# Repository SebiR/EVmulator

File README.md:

> [!CAUTION]
> This project includes dangerous voltages of 230V/400V, a bit of tinkering and (public) charging infrastructure.
> Build and use this project only if you know what you are doing. I am not liable for injuries or damages!

# EVmulator
A small PCB to go into IEC 62196 Typ 2 EV charging plugs to emulate a car to use a charging station as a normal outlet.

It's currently running with an ATTiny85, although an ATTiny25 will suffice. In the future it might be done with an ATTiny10.

## Features
* Two LEDs as status indicator
* Automatic switch from connected to charging
* 13 or 32A selectable current
* EVSE Pilot monitoring
* Completely powered by the pilot signal

## Function

The EVmulator simulates a connected car for the EVSE (electric vehicle supply equipment, the wallbox)

The EVSE outputs a 1kHz square wave signal with ±12V referenced to PE with 1000 ohms impedance on the CP (Control Pilot) pin and measures the voltage of the CP line.
As the EVmulator has a 1300 ohms resitor to PE, the positive voltage of the CP line is pulled to 9V and the EVSE detects a connected car.

After connecting, the EVmulator will detect the 1kHz PWM signal on the CP line and after approx. 5 seconds of PWM, the second restitor with 4.7kohms will be connected in parallel to the first resitor. As the voltage on the CP line drops to 6V, the EVSE will recognize the emulator as a charging car.

More information on Type 2 Signaling can be found here (in German):
https://www.goingelectric.de/wiki/Typ2-Signalisierung-und-Steckercodierung/

To end the charging process, a magnet is placed on the plug, opening a reed switch and signaling the end of charge to the charger.

## Usage

### Connection
Connect the three terminals of the EVmulator with the according pins of your IEC 62196 Type 2 male plug:

| Pin  | Function           | Description                                  |
|------|--------------------|----------------------------------------------|
| PP  | Control Pilot         | maximum current of the cable defined by a resistor |
| PE  | Earth | Commond ground for communication      |
| CP  | Control Pilot     | Communication line between car and charger |

### Solder Jumpers

There are two SMT solder jumpers located on the component side of the PCB:<br>
**SJ1** bypasses the internal reed switch in case you want to use a key switch or a push button to stop the charging process. Use NC (normally closed "openener" switches).<br>
**SJ2 LED** has to be closed after flashing the microcontroller to activate the status LED. The TPI programming interface is a bit finicky when it comes to other components on the programming lines.<br>

And there's one solder jumper on the side with the reed switch:<br>
**SJ3 13/32A** let's you select between a max. current of 13A or 32A depending on your application. Always make sure to use rated cables and connectors!

### Inside the plug

Drill a 3mm hole in the plug and put the LED through it. Fix the board with a bit of silicone or hot glue and you're done!

If you want, you can add a label:

### In the field
Just connect you Type 2 plug to the wallbox or charging station and authorize the charging process as you would normally.
The EVmulator will signal the charger that a car has been connected and that it is charging.<br>

To stop the charging process, place a magnet over the reed switch and unplug the plug.

| LED Behavior        | State      |
|---------------------|---------------|
| Quick blink (1 ms flash every ~32 ms) | Idling, waiting for CP signal          |
| Slow blink (1 ms flash every ~125 ms) | Checking if the CP signal is valid       |
| Very slow blink (1 ms flash every ~1 s) | Charging        |

## Firmware

The firmware is written for the ATTiny10 microcontroller using the Arduino IDE and the <a href="https://github.com/technoblogy/attiny10core">attiny10core</a> board definitions.

### Hardware Configuration

| Pin  | Function           | Description                                  |
|------|--------------------|----------------------------------------------|
| PB0  | LED Output         | Blinks to indicate system state              |
| PB1  | CHARGE_ON (Output) | Controls a MOSFET for to signal Charging state      |
| PB2  | Frequency Input     | Connected to external ~1kHz square wave, also Timer0 clock source |

### System Clock and Power Settings

- The system clock is derived from the 128 kHz Watchdog oscillator.
- A clock prescaler divides this to 32 kHz system frequency.
- The ADC and analog comparator are disabled to save power.
- The microcontroller primarily stays in `SLEEP_MODE_IDLE`, waking periodically via the Watchdog Timer interrupt.

### State Machine

The firmware operates in three states:

1. **IDLE**  
   - Wakes every ~32 ms via WDT.
   - If no external clock signal is detected (TCNT0 == 0), stays in IDLE.
   - If a clock signal is consistently present for 10 cycles, transitions to MEASURE.

2. **MEASURE**  
   - Wakes every ~125 ms.
   - Measures frequency using Timer0 (externally clocked).
   - If the frequency is above 500 Hz for 10 cycles, transitions to CHARGE.
   - Remains in MEASURE as long as signal is present and below 500 Hz.

3. **CHARGE**  
   - Wakes approximately every second.
   - Enables the CHARGE_ON MOSFET (PB1 high).
   - If frequency drops below 500 Hz for 5 consecutive cycles, reverts to MEASURE.

### LED Signal Behavior

The LED (on PB0) provides visual feedback for debugging and operational awareness:

| LED Behavior        | State(s)      | Meaning                                   |
|---------------------|---------------|-------------------------------------------|
| Quick blink (1 ms flash every ~32 ms) | IDLE          | Signal inactive or low frequency detected |
| Slow blink (1 ms flash every ~125 ms) | MEASURE       | Signal detected, measuring frequency       |
| Very slow blink (1 ms flash every ~1 s) | CHARGE        | Charging enabled, monitoring signal        |

All blinking is implemented by flashing the LED for 1 ms during each WDT interrupt.

### Power Optimization

- All unnecessary peripherals (ADC, comparator) are disabled.
- WDT interval is adjusted dynamically based on state.
- Sleep modes and minimal active time are used to reduce power consumption.
- Timer0 uses an asynchronous external clock, allowing operation even in low-power modes.

## Other

During development, I also created the <a href="https://github.com/SebiR/EVSE_Emulator_Shield">EVSE Emulator Shield</a> to test the EVmulator

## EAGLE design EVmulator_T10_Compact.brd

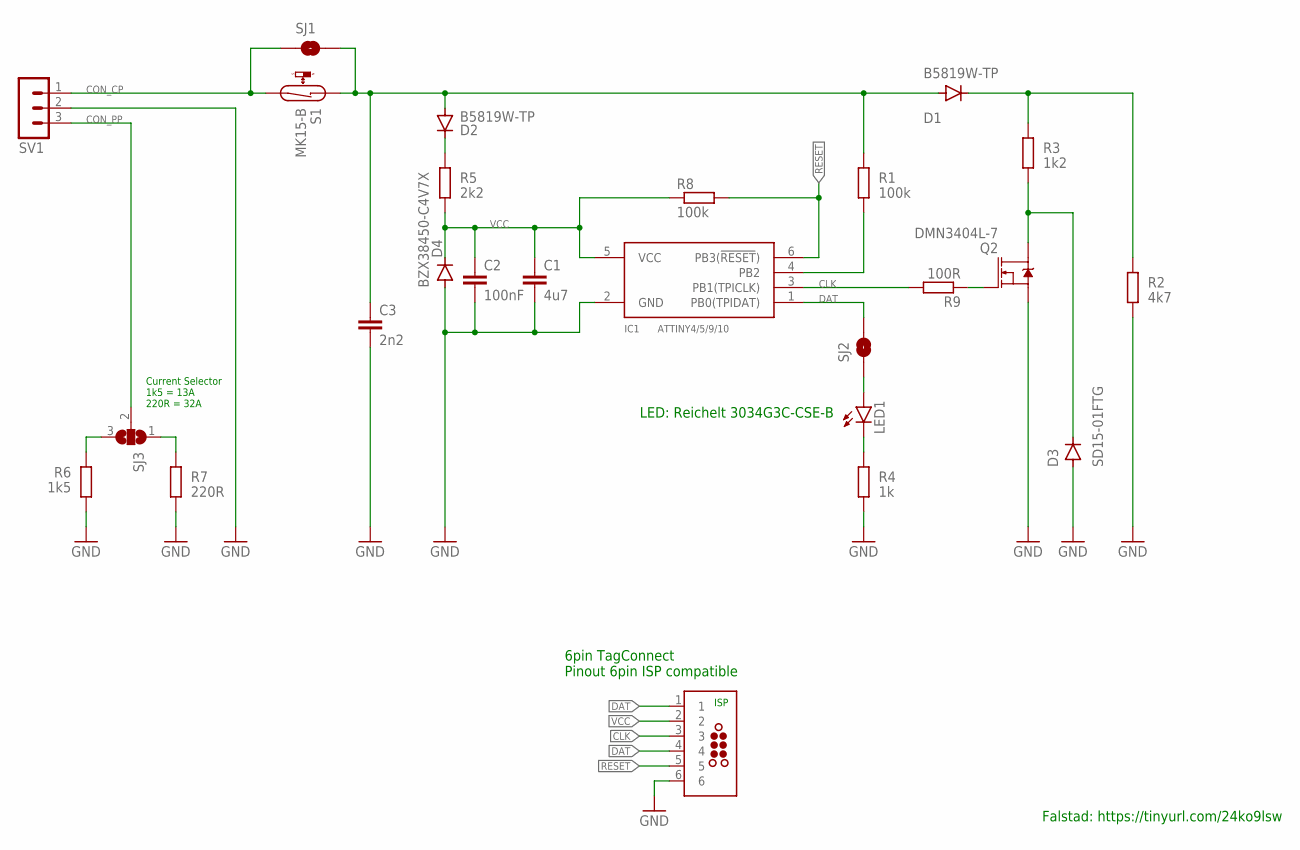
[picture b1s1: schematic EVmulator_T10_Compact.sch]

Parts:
C1: 4u7; C0603
C2: 100nF; C0603
C3: 2n2; C0603
D1, D2: B5819W-TP; SOD123
D3: SD15-01FTG; SOD323-W
D4: BZX38450-C4V7X; SOD323-W
IC1: ATTINY4/5/9/10; SOT23-6
J1: TAG-CONNECT_TC2030-MCP-NL
LED1: LED3MM
Q2: DMN3404L-7; SOT23-3
R1, R8: 100k; R0603
R2: 4k7; R0603
R3: 1k2; R0603
R4: 1k; R0603
R5: 2k2; R0603
R6: 1k5; R0805
R7: 220R; R0805
R9: 100R; R0603
S1: MK15-B; MK15
SJ1, SJ2: JUMPER-SMT_2_NO_SILK; SMT-JUMPER_2_NO_SILK
SJ3: SJ2W; SJ_2
SV1: MA03-1

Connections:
CLK: IC1.3 (PB1(TPICLK)), J1.3, R9.2
CON_CP: S1.2, SJ1.1, SV1.1
CON_PP: SJ3.2, SV1.3
CP: C3.1, D1.A, D2.A, R1.1, S1.1, SJ1.2
DAT: IC1.1 (PB0(TPIDAT)), J1.1, J1.4, SJ2.2
GND: C1.2, C2.2, C3.2, D3.A, D4.A, IC1.2 (GND), J1.6, Q2.2 (S), R2.1, R4.1, R6.1, R7.1, SV1.2
unnamed: Q2.1 (G), R9.1
unnamed: IC1.4 (PB2), R1.2
unnamed: D3.C, Q2.3 (D), R3.1
unnamed: LED1.K (C), R4.2
unnamed: D1.C, R2.2, R3.2
unnamed: D2.C, R5.2
unnamed: LED1.A, SJ2.1
unnamed: R6.2, SJ3.3
unnamed: R7.2, SJ3.1
RESET: IC1.6 (PB3(!RESET!)), J1.5, R8.2
VCC: C1.1, C2.1, D4.C, IC1.5 (VCC), J1.2, R5.1, R8.1

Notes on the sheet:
Falstad: https://tinyurl.com/24ko9lsw
Current Selector 1k5 = 13A 220R = 32A
ISP
6pin TagConnect Pinout 6pin ISP compatible
LED: Reichelt 3034G3C-CSE-B

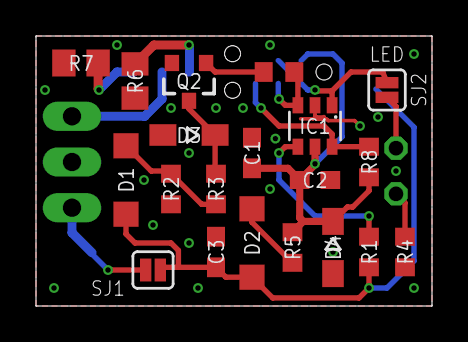
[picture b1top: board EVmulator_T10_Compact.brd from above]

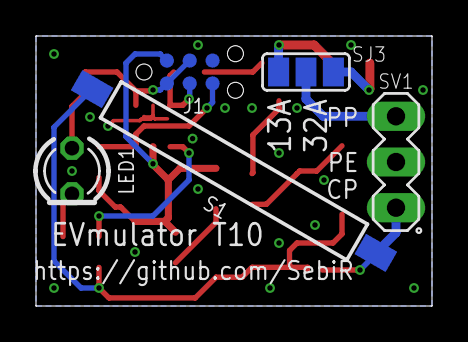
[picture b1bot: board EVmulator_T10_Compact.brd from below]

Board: 2 copper layers, 22.0 x 15.0 mm, 25 parts (5 on the bottom side), 17 nets.

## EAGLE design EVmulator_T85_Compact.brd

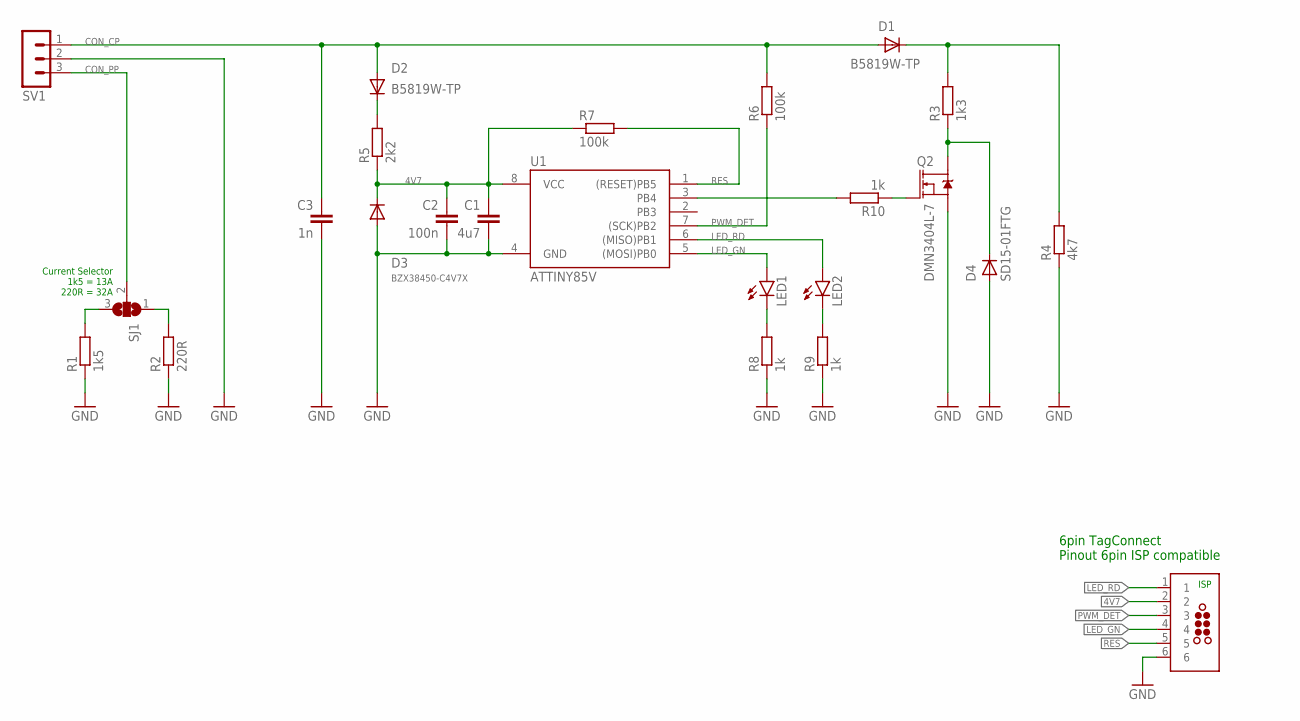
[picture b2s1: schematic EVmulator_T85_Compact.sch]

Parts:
C1: 4u7; C0603
C2: 100n; C0603
C3: 1n; C0603
D1, D2: B5819W-TP; SOD-123
D3: BZX38450-C4V7X; SOD-323F
D4: SD15-01FTG; SOD-323F
J1: TAG-CONNECT_TC2030-MCP-NL
LED1, LED2: LEDCHIP-LED0603; CHIP-LED0603
Q2: DMN3404L-7; SOT23-3
R1: 1k5; R0805
R2: 220R; R0805
R3: 1k3; R0603
R4: 4k7; R0603
R5: 2k2; R0603
R6, R7: 100k; R0603
R8, R9, R10: 1k; R0603
SJ1: SJ2W; SJ_2
SV1: MA03-1
U1: ATTINY85V; SOIC8

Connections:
4V7: C1.1, C2.1, D3.C, J1.2, R5.1, R7.1, U1.8 (VCC)
CON_CP: C3.1, D1.A, D2.A, R6.2, SV1.1
CON_PP: SJ1.2, SV1.3
GND: C1.2, C2.2, C3.2, D3.A, D4.A, J1.6, Q2.2 (S), R1.1, R2.1, R4.1, R8.1, R9.1, SV1.2, U1.4 (GND)
LED_GN: J1.4, LED1.A, U1.5 ((MOSI)PB0)
LED_RD: J1.1, LED2.A, U1.6 ((MISO)PB1)
unnamed: R1.2, SJ1.3
unnamed: R2.2, SJ1.1
unnamed: LED1.C, R8.2
unnamed: LED2.C, R9.2
unnamed: D4.C, Q2.3 (D), R3.1
unnamed: D1.C, R3.2, R4.2
unnamed: D2.C, R5.2
unnamed: Q2.1 (G), R10.1
unnamed: R10.2, U1.3 (PB4)
PWM_DET: J1.3, R6.1, U1.7 ((SCK)PB2)
RES: J1.5, R7.2, U1.1 ((RESET)PB5)

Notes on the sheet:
Current Selector 1k5 = 13A 220R = 32A
ISP
6pin TagConnect Pinout 6pin ISP compatible

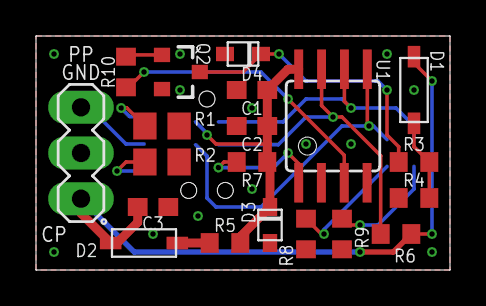
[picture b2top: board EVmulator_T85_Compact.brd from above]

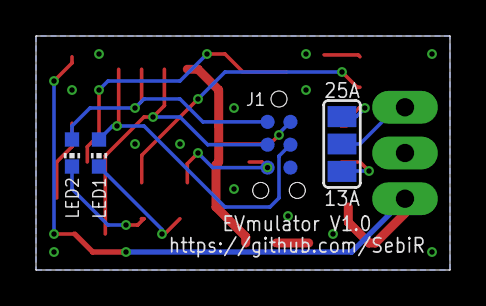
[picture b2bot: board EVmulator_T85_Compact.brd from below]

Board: 2 copper layers, 23.0 x 13.0 mm, 24 parts (4 on the bottom side), 17 nets.

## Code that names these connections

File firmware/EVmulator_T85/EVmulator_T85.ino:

/*

Fuses:
L 0xC4
H 0xD7
E 0xFF
WD. Osc. 128 kHz
*/

#include <avr/sleep.h>
#include <avr/power.h>
#include <avr/wdt.h>
#include <avr/io.h>
#include <util/delay.h>

#define LED_GN 0  // PB0 - Green indicator LED
#define LED_RD 1  // PB1 - Red indicator LED
#define CHARGE 4  // PB4 - MOSFET to activate second resistor

#define LED_ON_TIME 5 // in ms

int pwm_good_cntr = 0;
int pwm_bad_cntr = 0;
uint8_t pwm_status = 0;

// Blank WDT interrupt
ISR(WDT_vect) {
}

// Enter Sleep Mode
void enterSleep(void) {
  //  Unfortunately, power down stops the timers, so we can't use it
  //set_sleep_mode(SLEEP_MODE_PWR_DOWN);
  set_sleep_mode(SLEEP_MODE_IDLE);
  sleep_enable();
  sleep_mode();  // Start sleep mode

  // Nothing happens until WDT timeout

  sleep_disable();
  power_all_enable();
}

// Setup the Watch Dog Timer (WDT)
// http://modelleisenbahn-steuern.de/controller/atmega8/6-5-wdtcr-register-atmega8.htm
// https://www.best-microcontroller-projects.com/attiny-ultra-low-power.html
void setupWDT() {

  MCUSR &= ~(1 << WDRF);  // Clear the WDRF (Reset Flag).

  // Setting WDCE allows updates for 4 clock cycles end is needed to
  // change WDE or the watchdog pre-scalers.
  WDTCR |= (1 << WDCE) | (1 << WDE);

  // WD triggers every ~74ms
  WDTCR = (0 << WDP3) | (0 << WDP2) | (1 << WDP1) | (0 << WDP0);

  WDTCR |= _BV(WDIE);  // Enable the WDT interrupt.
}

//  Timer 0 is used as a counter to check the presence of the pilot PWM signal
void setupT0() {

  // Normal port operation, OC0A/OC0B disconnected, Normal Timer operation
  TCCR0A = (0 << COM0A1) | (0 << COM0A0) | (0 << COM0B1) | (0 << COM0B0) | (0 << WGM01) | (0 << WGM02);

  // Ext. T0 as input. Rising edge
  TCCR0B = 0;
  TCCR0B = (0 << FOC0A) | (0 << FOC0B) | (0 << WGM02) | (1 << CS02) | (1 << CS01) | (1 << CS00);
}


void setup() {

  pinMode(LED_GN, OUTPUT);
  pinMode(LED_RD, OUTPUT);
  pinMode(CHARGE, OUTPUT);

  // Unused pins as pulled up inputs
  pinMode(2, INPUT_PULLUP);
  pinMode(3, INPUT_PULLUP);

  digitalWrite(CHARGE, LOW);
  digitalWrite(LED_GN, LOW);
  digitalWrite(LED_RD, LOW);

  ADCSRA &= ~(1 << ADEN);  // Disable ADC

  setupT0();
  setupWDT();
}

void loop() {

  // Each 74ms -> 1kHz means 74 counts
  // 30 = 900Hz, 40 =1.2kHz
  if ((TCNT0 >= 60) && (TCNT0 <= 90)) {
    pwm_bad_cntr = 0;
    pwm_good_cntr++;
  } else {
    pwm_good_cntr = 0;
    pwm_bad_cntr++;
  }
  TCNT0 = 0;

  //  approx 5 seconds of good pwm and low flag
  //  74ms period time means ~15Hz
  if (pwm_good_cntr > 5 * 15 && pwm_status == 0) {
    pwm_status = 1;
    pwm_good_cntr = 0;
  } else if (pwm_bad_cntr > 5 * 15 && pwm_status == 1) {
    pwm_status = 0;
    pwm_bad_cntr = 0;
  }

  //  Pilot PWM signal is good, switch on charging indication resistor
  if (pwm_status == 1) {
    digitalWrite(LED_GN, HIGH);
    _delay_ms(LED_ON_TIME);
    digitalWrite(LED_GN, LOW);

    // Tell the EVSE we're changing from connected to charging
    digitalWrite(CHARGE, HIGH);

    // Pilot PWM signal lost, switch off charging resistor
  } else {
    digitalWrite(LED_RD, HIGH);
    _delay_ms(LED_ON_TIME);
    digitalWrite(LED_RD, LOW);

    // Signal the EVSE we're not charging but in connected mode
    digitalWrite(CHARGE, LOW);
  }

  //  Everything done, go to sleep
  enterSleep();
}

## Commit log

2023-09-03 * Started new HW Version (compact) * FW is running okay for the first try
2024-02-09 Finished compact version
2024-02-11 changed silkscreen for the 3pin header on both boards. Updated gerbers.
2024-02-11 increased silkscreen size on compact variant
2024-02-11 Made tValue Layer of compact variant more useful. Fixed airwire in compact variant
2024-02-11 * moved prototype board to deprecated (will not be maintained in the future= * added connection drawing to schematic, updated output
2024-02-11 started to explain the principle of operation
2024-02-11 added overview schematic
2024-02-11 fixed principle schematatic
2024-02-16 Re-organized firmware, removed some debugging left-overs
2024-02-16 Changed cycle time from 37 to 74ms -> more sleep, more better
2024-02-17 * minor tweaks in the FW * Started firmware flashing instructions
2024-03-04 Added WaveForms File
2025-04-29 *Added Tiny10 variant
2025-04-30 * small improvements
2025-04-30 * Modified Hardware
2025-06-03 Updated readme and schematics
2025-06-03 * Moved T85 FW do deprecated and added recent hex file
2025-06-04 * added label * updated documentation
2025-06-04 updated line breaks
2025-06-04 * Updated documentation
2025-06-04 Annotated schematic a bit more, created new PDF of schematics

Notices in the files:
parts and their libraries:
Eigene-Rietig: ©2009 ROFA.cz - modified and updated by Robert Darlington ‹rdarlington@gmail.com›
SparkFun-DiscreteSemi: Licensing: Creative Commons ShareAlike 4.0 International - https://creativecommons.org/licenses/by-sa/4.0
